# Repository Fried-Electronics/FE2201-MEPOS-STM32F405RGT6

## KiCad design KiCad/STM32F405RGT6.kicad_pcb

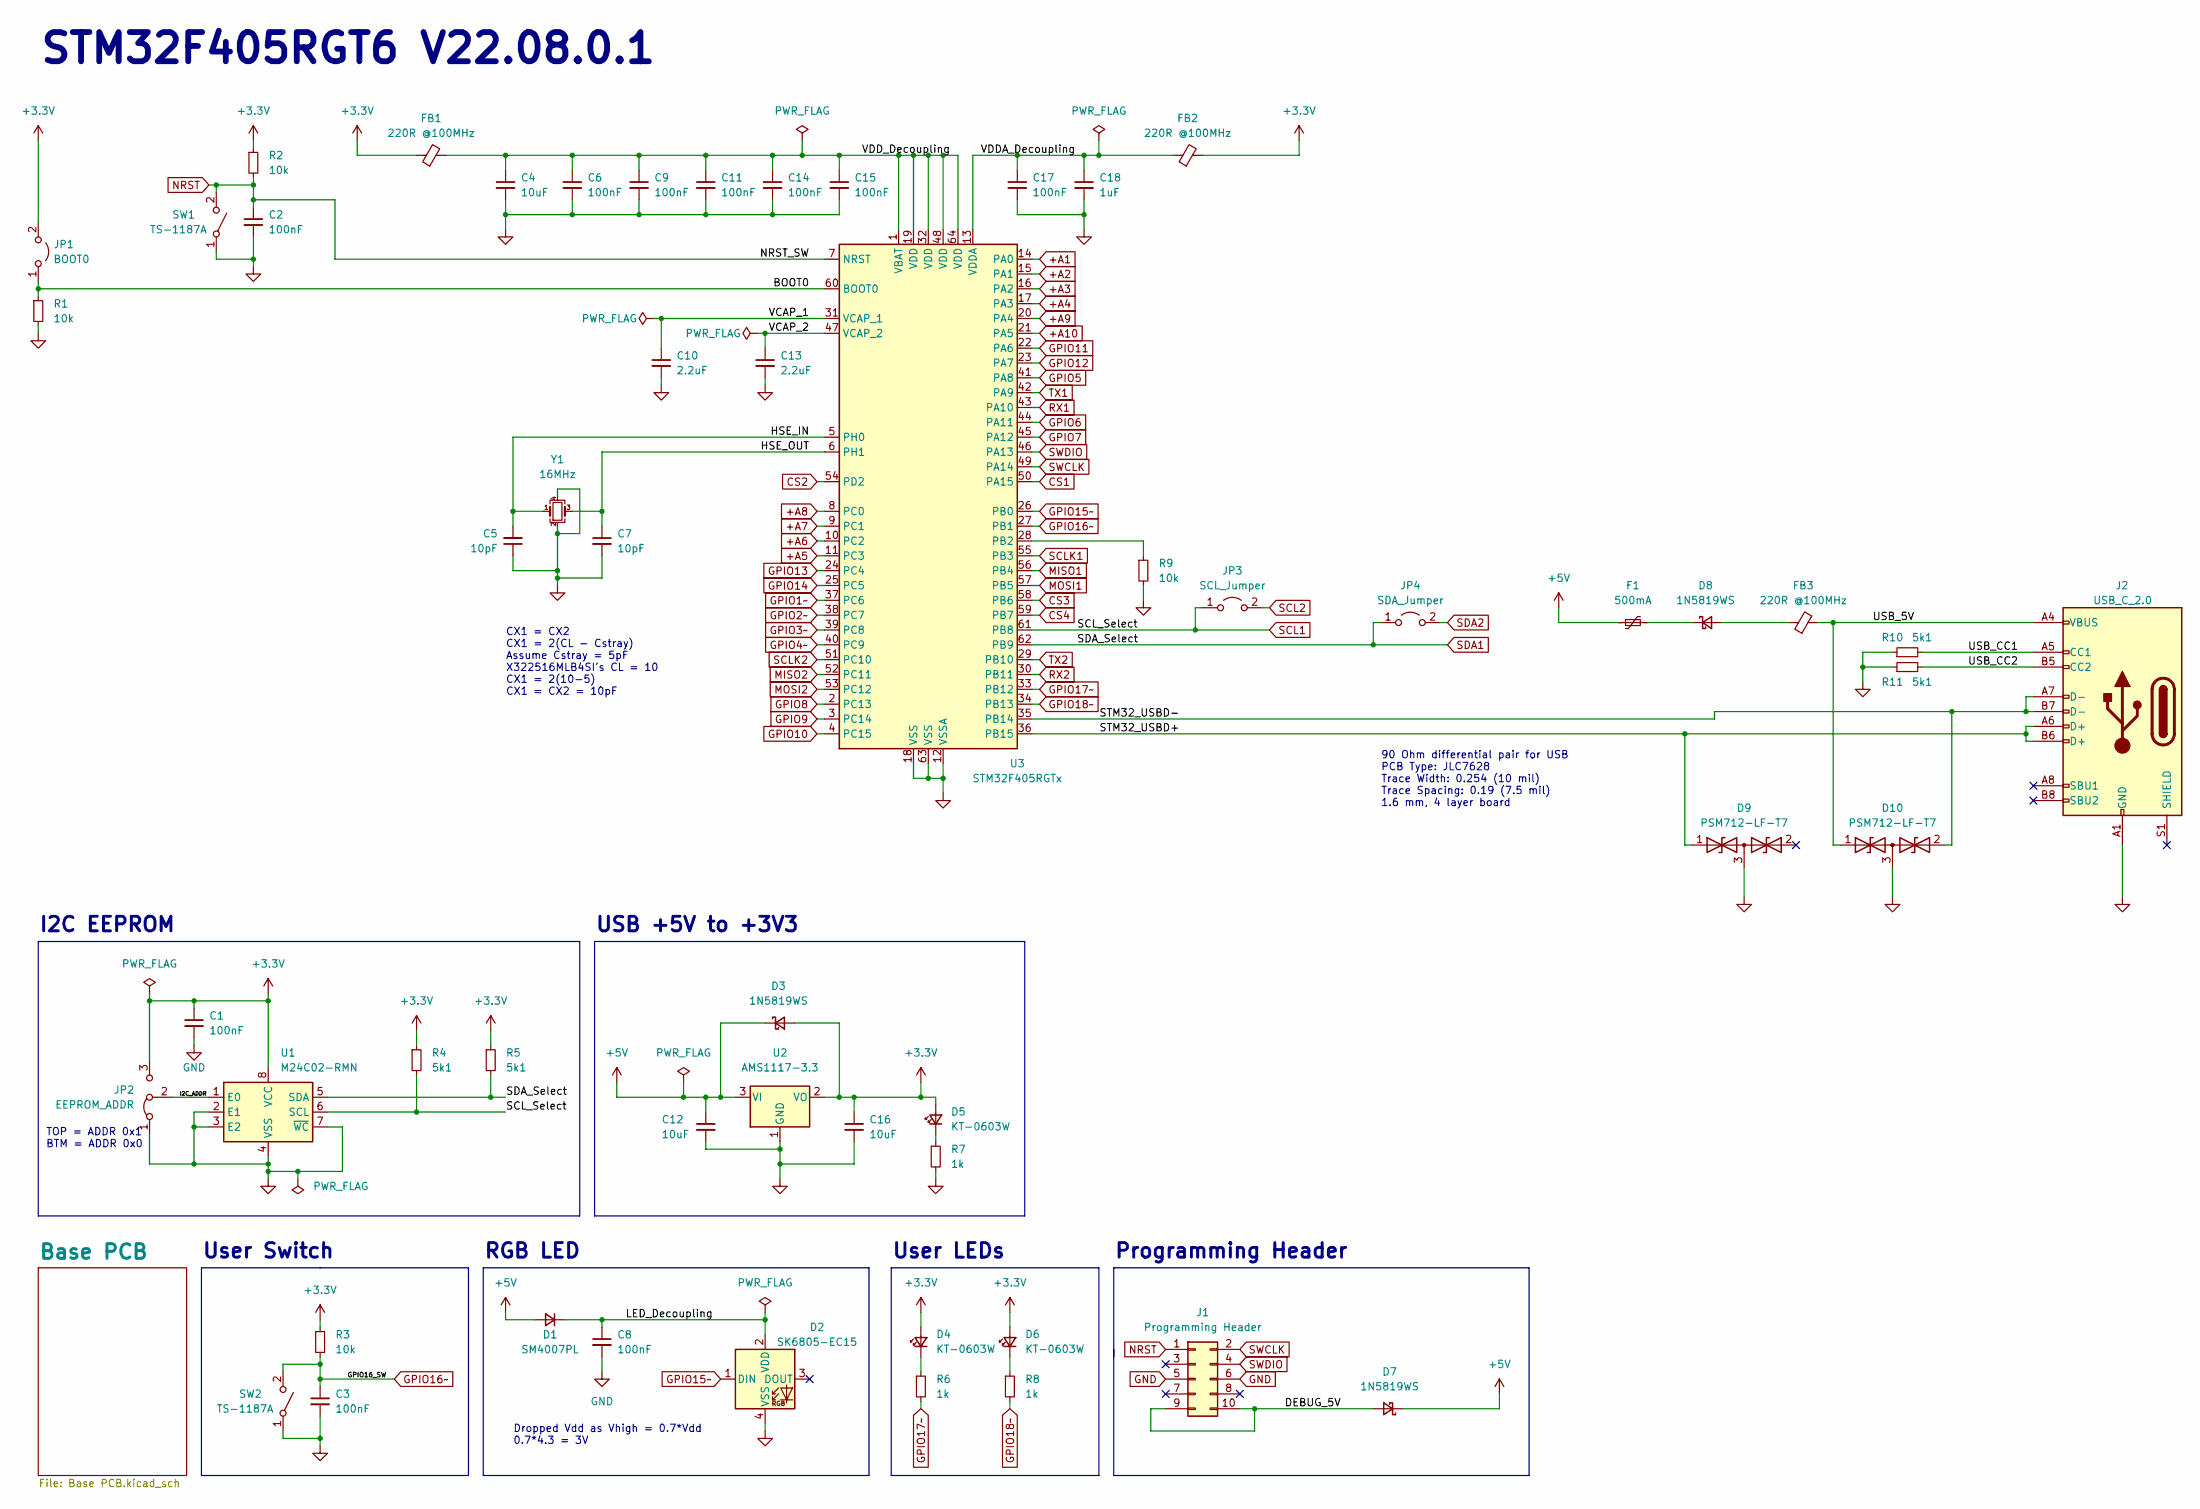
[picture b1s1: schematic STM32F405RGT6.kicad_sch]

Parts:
C1, C2, C3, C6, C8, C9, C11, C14, C15, C17: 100nF; C_0603_1608Metric; Part Number CC0603KRX7R9BB104; JLCPCB Part # C14663
C4, C12, C16: 10uF; C_0603_1608Metric; Part Number CL10A106KP8NNNC; JLCPCB Part # C19702
C5, C7: 10pF; C_0603_1608Metric; Part Number CL10C100JB8NNNC; JLCPCB Part # C1634
C10, C13: 2.2uF; C_0603_1608Metric; Part Number CL10A225KO8NNNC; JLCPCB Part # C23630
C18: 1uF; C_0603_1608Metric; Part Number CL10A105KB8NNNC; JLCPCB Part # C15849
D1: SM4007PL; D_SOD-123F; Part Number SM4007PL; JLCPCB Part # C64898
D2: SK6805-EC15
D3, D7, D8: 1N5819WS; D_SOD-323; Part Number 1N5819WS; JLCPCB Part # C191023
D4, D5, D6: KT-0603W; LED_0603_1608Metric; JLCPCB Part # C2290
D9, D10: PSM712-LF-T7; SOT-23; JLCPCB Part # C32677
F1: 500mA; Fuse_1206_3216Metric; Part Number JK-nSMD050-30; JLCPCB Part # C720075
FB1, FB2, FB3: 220R @100MHz; L_0603_1608Metric; Mouser Part Number 81-BLM18KG221SN1D
J1: Programming Header; PinHeader_2x05_P2.54mm_Horizontal; JLCPCB Part # C492433
J2: USB_C_2.0; USB_C_Receptacle_HRO_TYPE-C-31-M-12; Part Number TYPE-C-31-M-12; JLCPCB Part # C165948
JP1: BOOT0; PinHeader_1x02_P2.54mm_Vertical; Part Number PZ254V-11-02P; JLCPCB Part # C492401
JP2: EEPROM_ADDR; SolderJumper-3_P1.3mm_Bridged12_RoundedPad1.0x1.5mm
JP3: SCL_Jumper; SolderJumper-2_P1.3mm_Open_RoundedPad1.0x1.5mm
JP4: SDA_Jumper; SolderJumper-2_P1.3mm_Open_RoundedPad1.0x1.5mm
R1, R2, R3, R9: 10k; R_0603_1608Metric; Part Number 0603WAF1002T5E; JLCPCB Part # C25804
R4, R5, R10, R11: 5k1; R_0603_1608Metric; Part Number 0603WAF5101T5E; JLCPCB Part # C23186
R6, R7, R8: 1k; R_0603_1608Metric; Part Number 0603WAF1001T5E; JLCPCB Part # C21190
SW1, SW2: TS-1187A; SW_SPST_SKQG_WithStem; Part Number TS-1187A-B-A-B; JLCPCB Part # C318884
U1: M24C02-RMN; SOIC-8_3.9x4.9mm_P1.27mm; Mouser Part Number 511-M24C64-RMN6TP; JLCPCB Part # C79988
U2: AMS1117-3.3; SOT-223-3_TabPin2; Part Number AMS1117-3.3; JLCPCB Part # C6186
U3: STM32F405RGTx; LQFP-64_10x10mm_P0.5mm; Part Number STM32F405RGT6; JLCPCB Part # C15742
Y1: 16MHz; Crystal_SMD_3225-4Pin_3.2x2.5mm; Part Number X322516MLB4SI; JLCPCB Part # C13738

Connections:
+5V: C12.1, D1.2 (A), D3.1 (K), D7.1 (K), F1.1, U2.3 (VI); also elsewhere on the board
+A1: U3.14 (PA0); also elsewhere on the board
+A2: U3.15 (PA1); also elsewhere on the board
+A3: U3.16 (PA2); also elsewhere on the board
+A4: U3.17 (PA3); also elsewhere on the board
+A5: U3.11 (PC3); also elsewhere on the board
+A6: U3.10 (PC2); also elsewhere on the board
+A7: U3.9 (PC1); also elsewhere on the board
+A8: U3.8 (PC0); also elsewhere on the board
+A9: U3.20 (PA4); also elsewhere on the board
+A10: U3.21 (PA5); also elsewhere on the board
/BOOT0: JP1.1 (A), R1.1, U3.60 (BOOT0)
/DEBUG_5V: D7.2 (A), J1.9, J1.10
/HSE_IN: C5.2, U3.5 (PH0), Y1.1
/HSE_OUT: C7.1, U3.6 (PH1), Y1.3
/I2C_ADDR: JP2.2 (C), U1.1 (E0)
/LED_Decoupling: C8.1, D1.1 (K), D2.2 (VDD)
/STM32_USBD+: D9.1 (A1), J2.A6 (D+), J2.B6 (D+), U3.36 (PB15)
/STM32_USBD-: D10.2 (A2), J2.A7 (D-), J2.B7 (D-), U3.35 (PB14)
/USB_5V: D10.1 (A1), FB3.2, J2.A4 (VBUS), J2.A9 (VBUS), J2.B4 (VBUS), J2.B9 (VBUS)
/USB_CC1: J2.A5 (CC1), R10.2
/USB_CC2: J2.B5 (CC2), R11.2
/VCAP_1: C10.1, U3.31 (VCAP_1)
/VCAP_2: C13.1, U3.47 (VCAP_2)
/VDDA_Decoupling: C17.1, C18.1, FB2.1, U3.13 (VDDA)
/VDD_Decoupling: C4.1, C6.1, C9.1, C11.1, C14.1, C15.1, FB1.2, U3.1 (VBAT), U3.19 (VDD), U3.32 (VDD), U3.48 (VDD), U3.64 (VDD)
CS1: U3.50 (PA15); also elsewhere on the board
CS2: U3.54 (PD2); also elsewhere on the board
CS3: U3.58 (PB6); also elsewhere on the board
CS4: U3.59 (PB7); also elsewhere on the board
GND: C1.2, C2.2, C3.2, C4.2, C5.1, C6.2, C7.2, C8.2, C9.2, C10.2, C11.2, C12.2, C13.2, C14.2, C15.2, C16.2, C17.2, C18.2, D2.4 (VSS), D9.3 (common), D10.3 (common), J1.5, J1.6, J2.A1 (GND), J2.A12 (GND), J2.B1 (GND), J2.B12 (GND), JP2.1 (A), R1.2, R7.2, R9.2, R10.1, R11.1, SW1.1 (A), SW2.1 (A), U1.2 (E1), U1.3 (E2), U1.4 (VSS), U1.7 (~WC), U2.1 (GND), U3.12 (VSSA), U3.18 (VSS), U3.63 (VSS), Y1.2, Y1.4; also elsewhere on the board
GPIO1~: U3.37 (PC6); also elsewhere on the board
GPIO2~: U3.38 (PC7); also elsewhere on the board
GPIO3~: U3.39 (PC8); also elsewhere on the board
GPIO4~: U3.40 (PC9); also elsewhere on the board
GPIO5: U3.41 (PA8); also elsewhere on the board
GPIO6: U3.44 (PA11); also elsewhere on the board
GPIO7: U3.45 (PA12); also elsewhere on the board
GPIO8: U3.2 (PC13); also elsewhere on the board
GPIO9: U3.3 (PC14); also elsewhere on the board
GPIO10: U3.4 (PC15); also elsewhere on the board
GPIO11: U3.22 (PA6); also elsewhere on the board
GPIO12: U3.23 (PA7); also elsewhere on the board
GPIO13: U3.24 (PC4); also elsewhere on the board
GPIO14: U3.25 (PC5); also elsewhere on the board
GPIO15~: D2.1 (DIN), U3.26 (PB0); also elsewhere on the board
GPIO16~: C3.1, R3.2, SW2.2 (B), U3.27 (PB1); also elsewhere on the board
GPIO17~: R6.2, U3.33 (PB12); also elsewhere on the board
GPIO18~: R8.2, U3.34 (PB13); also elsewhere on the board
MISO1: U3.56 (PB4); also elsewhere on the board
MISO2: U3.52 (PC11); also elsewhere on the board
MOSI1: U3.57 (PB5); also elsewhere on the board
MOSI2: U3.53 (PC12); also elsewhere on the board
NRST: C2.1, J1.1, R2.2, SW1.2 (B), U3.7 (NRST)
unnamed: D4.1 (K), R6.1
unnamed: D5.1 (K), R7.1
unnamed: D6.1 (K), R8.1
unnamed: D8.1 (K), F1.2
unnamed: D8.2 (A), FB3.1
unnamed: R9.1, U3.28 (PB2)
RX1: U3.43 (PA10); also elsewhere on the board
RX2: U3.30 (PB11); also elsewhere on the board
SCL1: JP3.1 (A), R4.2, U1.6 (SCL), U3.61 (PB8); also elsewhere on the board
SCL2: JP3.2 (B); also elsewhere on the board
SCLK1: U3.55 (PB3); also elsewhere on the board
SCLK2: U3.51 (PC10); also elsewhere on the board
SDA1: JP4.1 (A), R5.2, U1.5 (SDA), U3.62 (PB9); also elsewhere on the board
SDA2: JP4.2 (B); also elsewhere on the board
SWCLK: J1.2, U3.49 (PA14)
SWDIO: J1.4, U3.46 (PA13)
TX1: U3.42 (PA9); also elsewhere on the board
TX2: U3.29 (PB10); also elsewhere on the board

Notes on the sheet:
USB +5V to +3V3
CX1 = CX2 CX1 = 2(CL - Cstray) Assume Cstray = 5pF X322516MLB4SI's CL = 10 CX1 = 2(10-5) CX1 = CX2 = 10pF
User LEDs
RGB LED
TOP = ADDR 0x1 BTM = ADDR 0x0
STM32F405RGT6 V22.08.0.1
I2C EEPROM
Programming Header
Dropped Vdd as Vhigh = 0.7*Vdd 0.7*4.3 = 3V
User Switch
90 Ohm differential pair for USB PCB Type: JLC7628 Trace Width: 0.254 (10 mil) Trace Spacing: 0.19 (7.5 mil) 1.6 mm, 4 layer board

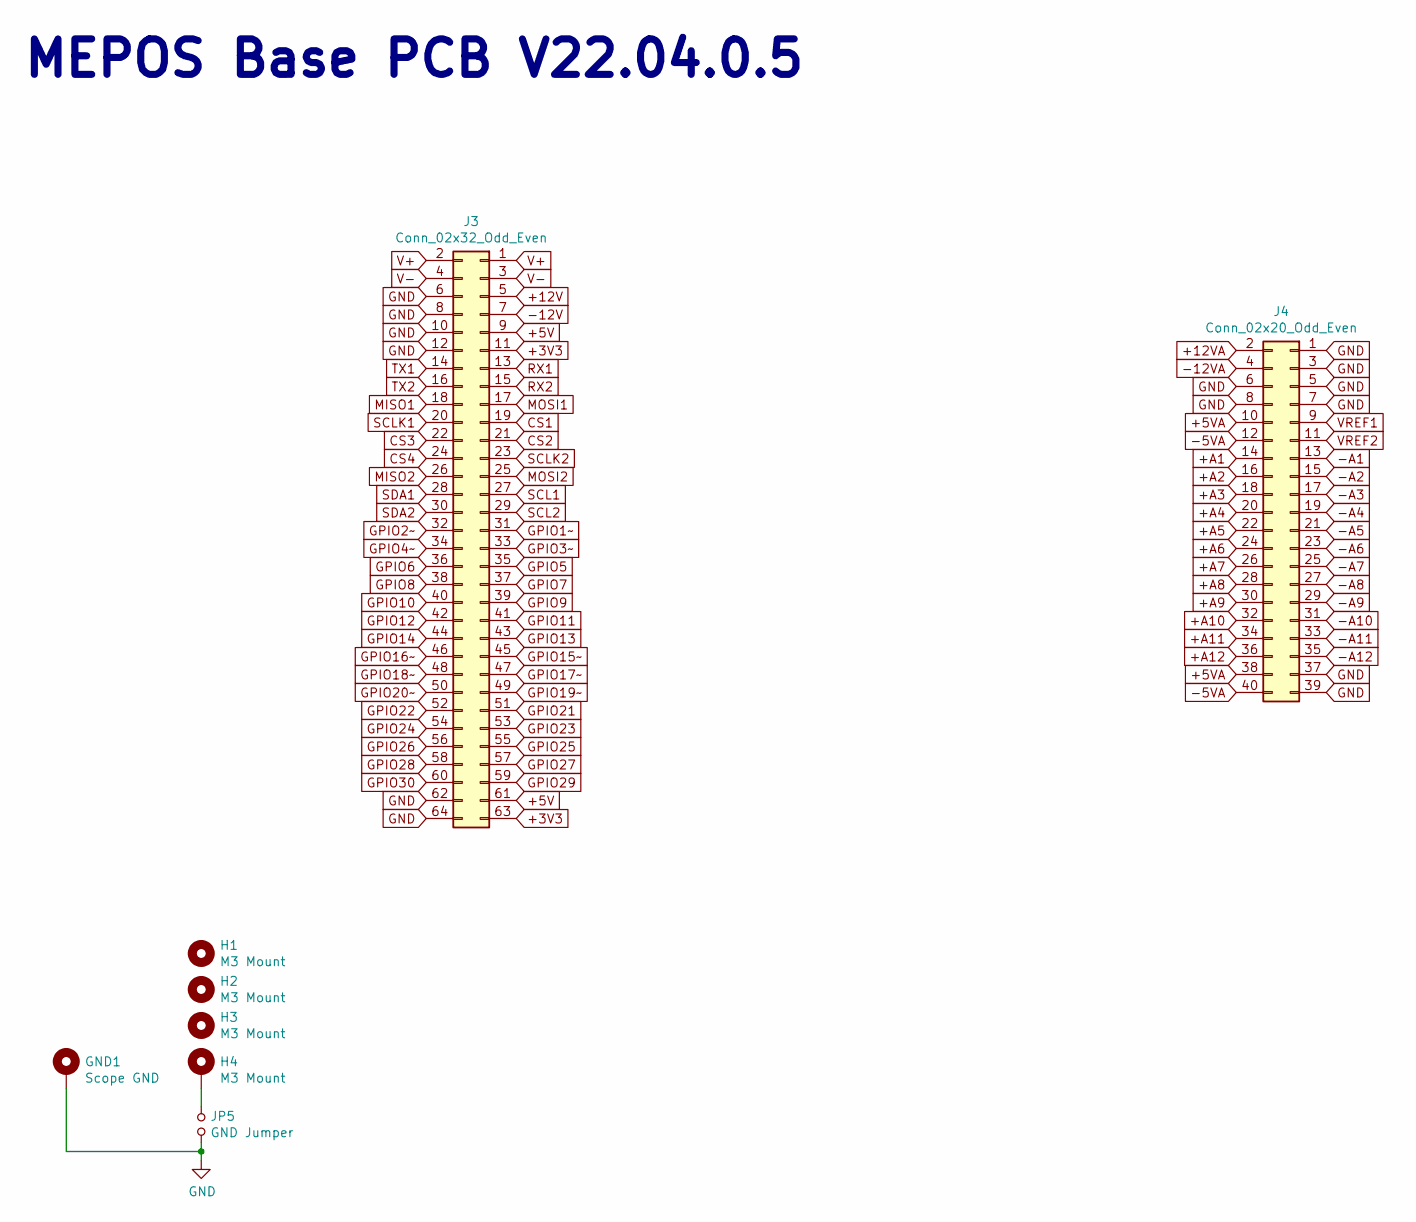
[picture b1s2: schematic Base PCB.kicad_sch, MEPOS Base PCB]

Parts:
GND1: Scope GND; Scope_GND
H1, H2, H3, H4: M3 Mount; MountingHole_3.2mm_M3_Pad
J3: Conn_02x32_Odd_Even; PinSocket_2x32_P2.54mm_Vertical
J4: Conn_02x20_Odd_Even; PinSocket_2x20_P2.54mm_Vertical
JP5: GND Jumper; TestPoint_2Pads_Pitch2.54mm_Drill0.8mm

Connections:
+5V: J3.9, J3.61; also elsewhere on the board
+5VA: J4.10, J4.38
+12V: J3.5
+12VA: J4.2
+A1: J4.14; also elsewhere on the board
+A2: J4.16; also elsewhere on the board
+A3: J4.18; also elsewhere on the board
+A4: J4.20; also elsewhere on the board
+A5: J4.22; also elsewhere on the board
+A6: J4.24; also elsewhere on the board
+A7: J4.26; also elsewhere on the board
+A8: J4.28; also elsewhere on the board
+A9: J4.30; also elsewhere on the board
+A10: J4.32; also elsewhere on the board
+A11: J4.34
+A12: J4.36
-5VA: J4.12, J4.40
-12V: J3.7
-12VA: J4.4
-A1: J4.13
-A2: J4.15
-A3: J4.17
-A4: J4.19
-A5: J4.21
-A6: J4.23
-A7: J4.25
-A8: J4.27
-A9: J4.29
-A10: J4.31
-A11: J4.33
-A12: J4.35
CS1: J3.19; also elsewhere on the board
CS2: J3.21; also elsewhere on the board
CS3: J3.22; also elsewhere on the board
CS4: J3.24; also elsewhere on the board
GND: GND1.1, J3.6, J3.8, J3.10, J3.12, J3.62, J3.64, J4.1, J4.3, J4.5, J4.6, J4.7, J4.8, J4.37, J4.39, JP5.2; also elsewhere on the board
GPIO1~: J3.31; also elsewhere on the board
GPIO2~: J3.32; also elsewhere on the board
GPIO3~: J3.33; also elsewhere on the board
GPIO4~: J3.34; also elsewhere on the board
GPIO5: J3.35; also elsewhere on the board
GPIO6: J3.36; also elsewhere on the board
GPIO7: J3.37; also elsewhere on the board
GPIO8: J3.38; also elsewhere on the board
GPIO9: J3.39; also elsewhere on the board
GPIO10: J3.40; also elsewhere on the board
GPIO11: J3.41; also elsewhere on the board
GPIO12: J3.42; also elsewhere on the board
GPIO13: J3.43; also elsewhere on the board
GPIO14: J3.44; also elsewhere on the board
GPIO15~: J3.45; also elsewhere on the board
GPIO16~: J3.46; also elsewhere on the board
GPIO17~: J3.47; also elsewhere on the board
GPIO18~: J3.48; also elsewhere on the board
GPIO19~: J3.49
GPIO20~: J3.50
GPIO21: J3.51
GPIO22: J3.52
GPIO23: J3.53
GPIO24: J3.54
GPIO25: J3.55
GPIO26: J3.56
GPIO27: J3.57
GPIO28: J3.58
GPIO29: J3.59
GPIO30: J3.60
MISO1: J3.18; also elsewhere on the board
MISO2: J3.26; also elsewhere on the board
MOSI1: J3.17; also elsewhere on the board
MOSI2: J3.25; also elsewhere on the board
unnamed: H4.1, JP5.1
RX1: J3.13; also elsewhere on the board
RX2: J3.15; also elsewhere on the board
SCL1: J3.27; also elsewhere on the board
SCL2: J3.29; also elsewhere on the board
SCLK1: J3.20; also elsewhere on the board
SCLK2: J3.23; also elsewhere on the board
SDA1: J3.28; also elsewhere on the board
SDA2: J3.30; also elsewhere on the board
TX1: J3.14; also elsewhere on the board
TX2: J3.16; also elsewhere on the board
V+: J3.1, J3.2
V-: J3.3, J3.4
VREF1: J4.9
VREF2: J4.11

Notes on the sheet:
MEPOS Base PCB V22.04.0.5

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
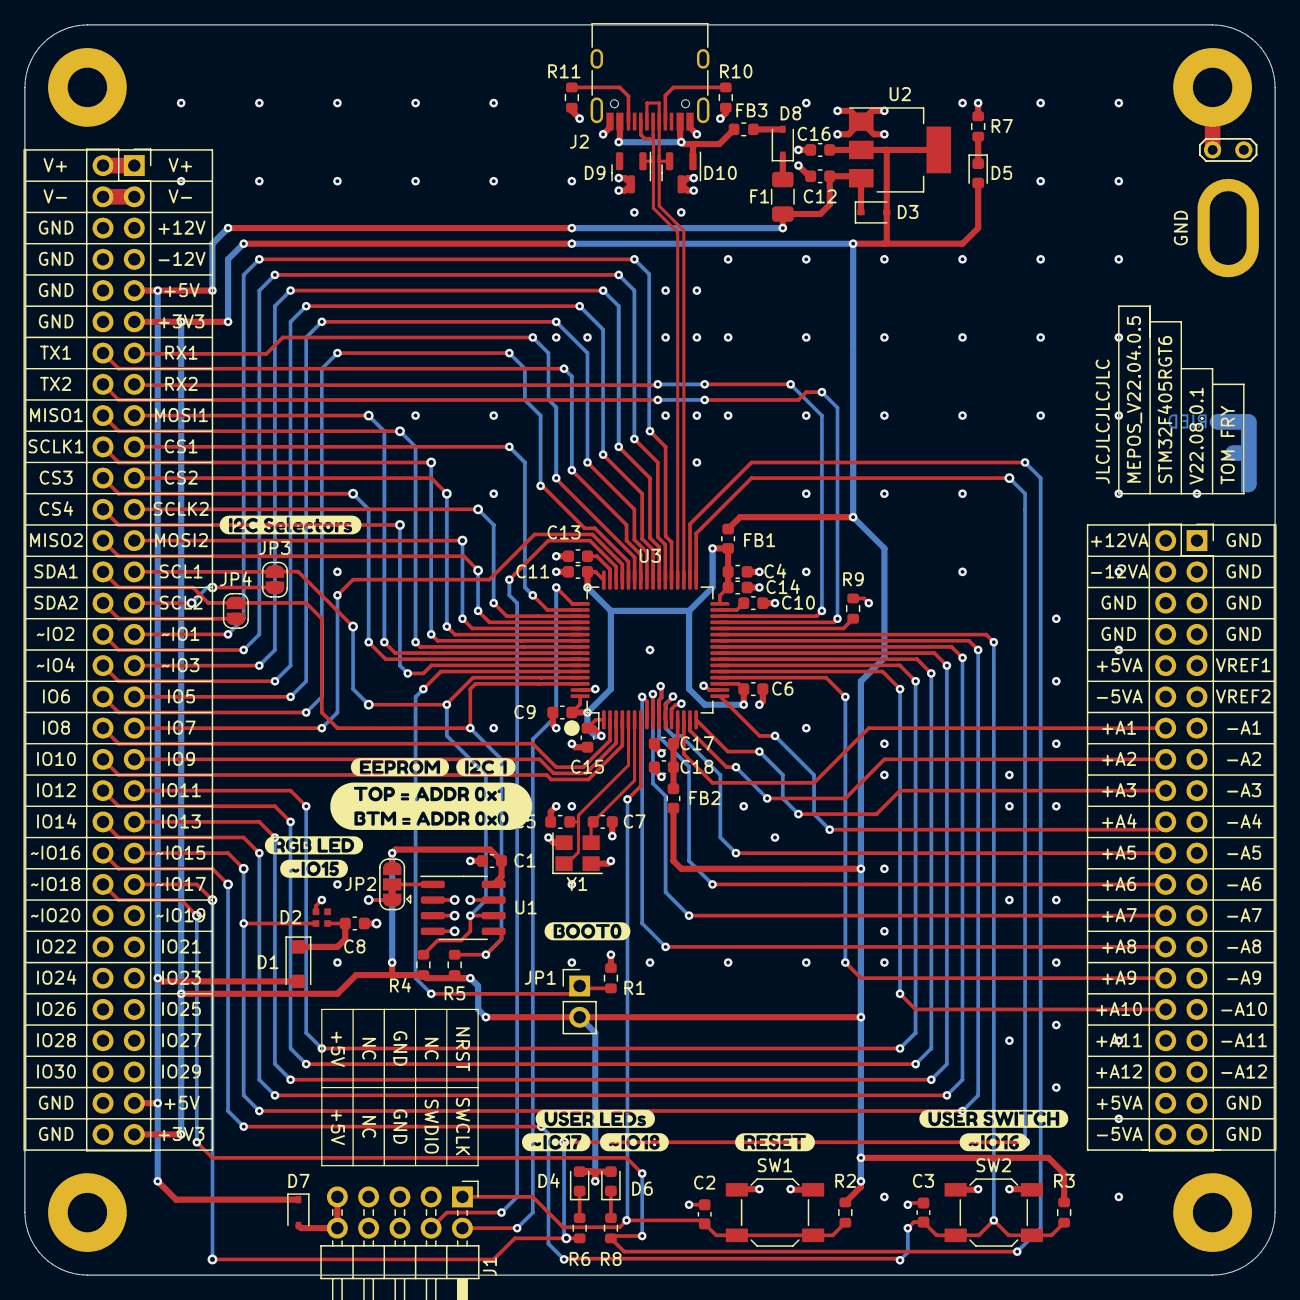
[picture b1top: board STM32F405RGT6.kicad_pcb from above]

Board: 4 copper layers, 101.6 x 101.6 mm, 77 parts (1 on the bottom side), 78 nets.

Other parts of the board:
KiCad_Logo: KiCad-Logo2_5mm_SilkScreen
kibuzzard-630B16ED: G***; kibuzzard-630B16ED
kibuzzard-630B17C2: G***; kibuzzard-630B17C2
kibuzzard-630B17D9: G***; kibuzzard-630B17D9
kibuzzard-630B17E2: G***; kibuzzard-630B17E2
kibuzzard-630B175D: G***; kibuzzard-630B175D
kibuzzard-630B176C: G***; kibuzzard-630B176C
kibuzzard-630B178A: G***; kibuzzard-630B178A
kibuzzard-630B1710: G***; kibuzzard-630B1710
kibuzzard-630B1728: G***; kibuzzard-630B1728
kibuzzard-630B1736: G***; kibuzzard-630B1736
kibuzzard-630B1749: G***; kibuzzard-630B1749
kibuzzard-630B1806: G***; kibuzzard-630B1806
kibuzzard-632AC88F: G***; kibuzzard-632AC88F

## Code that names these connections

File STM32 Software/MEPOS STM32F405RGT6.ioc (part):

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Mcu.Name=STM32F405RGTx
Mcu.Package=LQFP64
Mcu.UserName=STM32F405RGTx
PA0-WKUP.GPIOParameters=GPIO_Label
PA0-WKUP.GPIO_Label=A1
PA0-WKUP.Signal=ADCx_IN0
PA1.GPIOParameters=GPIO_Label
PA1.GPIO_Label=A2
PA1.Signal=ADCx_IN1
PA10.GPIOParameters=GPIO_Label
PA10.GPIO_Label=RX1
PA10.Mode=Asynchronous
PA10.Signal=USART1_RX
PA11.GPIOParameters=GPIO_Label
PA11.GPIO_Label=GPIO6
PA11.Signal=GPIO_Output
PA12.GPIOParameters=GPIO_Label
PA12.GPIO_Label=GPIO7
PA12.Signal=GPIO_Output
PA13.GPIOParameters=GPIO_Label
PA13.GPIO_Label=SWDIO
PA13.Mode=Trace_Asynchronous_SW
PA13.Signal=SYS_JTMS-SWDIO
PA14.GPIOParameters=GPIO_Label
PA14.GPIO_Label=SWCLK
PA14.Mode=Trace_Asynchronous_SW
PA14.Signal=SYS_JTCK-SWCLK
PA15.GPIOParameters=GPIO_Label
PA15.GPIO_Label=GPIO8
PA15.Signal=S_TIM2_CH1_ETR
PA2.GPIOParameters=GPIO_Label
PA2.GPIO_Label=A3
PA2.Signal=ADCx_IN2
PA3.GPIOParameters=GPIO_Label
PA3.GPIO_Label=A4
PA3.Signal=ADCx_IN3
PA4.GPIOParameters=GPIO_Label
PA4.GPIO_Label=A9
PA4.Signal=COMP_DAC1_group
PA5.GPIOParameters=GPIO_Label
PA5.GPIO_Label=A10
PA5.Signal=COMP_DAC2_group
PA6.GPIOParameters=GPIO_Label
PA6.GPIO_Label=GPIO15
PA6.Signal=GPIO_Output
PA7.GPIOParameters=GPIO_Label
PA7.GPIO_Label=GPIO16
PA7.Signal=GPIO_Output
PA8.GPIOParameters=GPIO_Label
PA8.GPIO_Label=GPIO5
PA8.Signal=S_TIM1_CH1
PA9.GPIOParameters=GPIO_Label
PA9.GPIO_Label=TX1
PA9.Mode=Asynchronous
PA9.Signal=USART1_TX
PB0.GPIOParameters=GPIO_Label
PB0.GPIO_Label=GPIO19~
PB0.Signal=GPIO_Output
PB1.GPIOParameters=GPIO_Label
PB1.GPIO_Label=GPIO20~
PB1.Signal=GPIO_Output
PB10.GPIOParameters=GPIO_Label
PB10.GPIO_Label=TX2
PB10.Mode=Asynchronous
PB10.Signal=USART3_TX
PB11.GPIOParameters=GPIO_Label
PB11.GPIO_Label=RX2
PB11.Mode=Asynchronous
PB11.Signal=USART3_RX
PB12.GPIOParameters=GPIO_Label
PB12.GPIO_Label=GPIO21
PB12.Mode=CAN_Activate
PB12.Signal=CAN2_RX
PB13.GPIOParameters=GPIO_Label
PB13.GPIO_Label=GPIO22
PB13.Mode=CAN_Activate
PB13.Signal=CAN2_TX
PB14.Mode=Device_Only_FS
PB14.Signal=USB_OTG_HS_DM
PB15.Mode=Device_Only_FS
PB15.Signal=USB_OTG_HS_DP
PB2.GPIOParameters=GPIO_Label
PB2.GPIO_Label=BOOT1
PB2.Signal=GPIO_Input
PB3.GPIOParameters=GPIO_Label
PB3.GPIO_Label=SWO
PB3.Mode=Trace_Asynchronous_SW
PB3.Signal=SYS_JTDO-SWO
PB4.GPIOParameters=GPIO_Label
PB4.GPIO_Label=CS2
PB4.Signal=GPIO_Output
PB5.GPIOParameters=GPIO_Label
PB5.GPIO_Label=GPIO9
PB5.Signal=GPIO_Output
PB6.GPIOParameters=GPIO_Label
PB6.GPIO_Label=GPIO10
PB6.Signal=GPIO_Output
PB7.GPIOParameters=GPIO_Label
PB7.GPIO_Label=GPIO11
PB7.Signal=GPIO_Output
PB8.GPIOParameters=GPIO_Label
PB8.GPIO_Label=SCL1
PB8.Mode=I2C
PB8.Signal=I2C1_SCL
PB9.GPIOParameters=GPIO_Label
PB9.GPIO_Label=SDA1
PB9.Mode=I2C
PB9.Signal=I2C1_SDA
PC0.GPIOParameters=GPIO_Label
PC0.GPIO_Label=A8
PC0.Signal=ADCx_IN10
PC1.GPIOParameters=GPIO_Label
PC1.GPIO_Label=A7
PC1.Signal=ADCx_IN11
PC10.GPIOParameters=GPIO_Label
PC10.GPIO_Label=SCLK1
PC10.Mode=Full_Duplex_Master
PC10.Signal=SPI3_SCK
PC11.GPIOParameters=GPIO_Label
PC11.GPIO_Label=MISO1
PC11.Mode=Full_Duplex_Master
PC11.Signal=SPI3_MISO
PC12.GPIOParameters=GPIO_Label
PC12.GPIO_Label=MOSI1
PC12.Mode=Full_Duplex_Master
PC12.Signal=SPI3_MOSI
PC13-ANTI_TAMP.GPIOParameters=GPIO_Label
PC13-ANTI_TAMP.GPIO_Label=GPIO12
PC13-ANTI_TAMP.Signal=GPIO_Output
PC14-OSC32_IN.GPIOParameters=GPIO_Label
PC14-OSC32_IN.GPIO_Label=GPIO13
PC14-OSC32_IN.Signal=GPIO_Output
PC15-OSC32_OUT.GPIOParameters=GPIO_Label
PC15-OSC32_OUT.GPIO_Label=GPIO14
PC15-OSC32_OUT.Signal=GPIO_Output
PC2.GPIOParameters=GPIO_Label
PC2.GPIO_Label=A6
PC2.Signal=ADCx_IN12
PC3.GPIOParameters=GPIO_Label
PC3.GPIO_Label=A5
PC3.Signal=ADCx_IN13
PC4.GPIOParameters=GPIO_Label
PC4.GPIO_Label=GPIO17~
PC4.Signal=GPIO_Output
PC5.GPIOParameters=GPIO_Label
PC5.GPIO_Label=GPIO18~
PC5.Signal=GPIO_Output
PC6.GPIOParameters=GPIO_Label
PC6.GPIO_Label=GPIO1~
PC6.Signal=S_TIM3_CH1
PC7.GPIOParameters=GPIO_Label
PC7.GPIO_Label=GPIO2~
PC7.Signal=S_TIM3_CH2
PC8.GPIOParameters=GPIO_Label
PC8.GPIO_Label=GPIO3~
PC8.Signal=S_TIM3_CH3
PC9.GPIOParameters=GPIO_Label
PC9.GPIO_Label=GPIO4~
PC9.Signal=S_TIM3_CH4
PD2.GPIOParameters=GPIO_Label
PD2.GPIO_Label=CS1
PD2.Signal=GPIO_Output
PH0-OSC_IN.Mode=HSE-External-Oscillator
PH0-OSC_IN.Signal=RCC_OSC_IN
PH1-OSC_OUT.Mode=HSE-External-Oscillator
PH1-OSC_OUT.Signal=RCC_OSC_OUT
RCC.HSE_VALUE=25000000
RCC.SYSCLKFreq_VALUE=168000000
RCC.SYSCLKSource=RCC_SYSCLKSOURCE_PLLCLK
board=custom

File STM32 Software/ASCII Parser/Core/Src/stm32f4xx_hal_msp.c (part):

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    __HAL_RCC_GPIOC_CLK_ENABLE();
    __HAL_RCC_GPIOA_CLK_ENABLE();
    /**ADC1 GPIO Configuration
    PC0     ------> ADC1_IN10
    PC1     ------> ADC1_IN11
    PC2     ------> ADC1_IN12
    PC3     ------> ADC1_IN13
    PA0-WKUP     ------> ADC1_IN0
    PA1     ------> ADC1_IN1
    PA2     ------> ADC1_IN2
    PA3     ------> ADC1_IN3
    */
    GPIO_InitStruct.Pin = A8_Pin|A7_Pin|A6_Pin|A5_Pin;
    GPIO_InitStruct.Mode = GPIO_MODE_ANALOG;
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    __HAL_RCC_ADC1_CLK_DISABLE();

    /**ADC1 GPIO Configuration
    PC0     ------> ADC1_IN10
    PC1     ------> ADC1_IN11
    PC2     ------> ADC1_IN12
    PC3     ------> ADC1_IN13
    PA0-WKUP     ------> ADC1_IN0
    PA1     ------> ADC1_IN1
    PA2     ------> ADC1_IN2
    PA3     ------> ADC1_IN3
    */
    HAL_GPIO_DeInit(GPIOC, A8_Pin|A7_Pin|A6_Pin|A5_Pin);

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
    __HAL_RCC_GPIOB_CLK_ENABLE();
    /**CAN2 GPIO Configuration
    PB12     ------> CAN2_RX
    PB13     ------> CAN2_TX
    */
    GPIO_InitStruct.Pin = GPIO17__Pin|GPIO18__Pin;
    GPIO_InitStruct.Mode = GPIO_MODE_AF_PP;
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    __HAL_RCC_CAN1_CLK_DISABLE();

    /**CAN2 GPIO Configuration
    PB12     ------> CAN2_RX
    PB13     ------> CAN2_TX
    */
    HAL_GPIO_DeInit(GPIOB, GPIO17__Pin|GPIO18__Pin);

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
    __HAL_RCC_GPIOA_CLK_ENABLE();
    /**DAC GPIO Configuration
    PA4     ------> DAC_OUT1
    PA5     ------> DAC_OUT2
    */
    GPIO_InitStruct.Pin = A9_Pin|A10_Pin;
    GPIO_InitStruct.Mode = GPIO_MODE_ANALOG;
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    __HAL_RCC_DAC_CLK_DISABLE();

    /**DAC GPIO Configuration
    PA4     ------> DAC_OUT1
    PA5     ------> DAC_OUT2
    */
    HAL_GPIO_DeInit(GPIOA, A9_Pin|A10_Pin);

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
    __HAL_RCC_GPIOB_CLK_ENABLE();
    /**I2C1 GPIO Configuration
    PB8     ------> I2C1_SCL
    PB9     ------> I2C1_SDA
    */
    GPIO_InitStruct.Pin = SCL1_2_Pin|SDA1_2_Pin;
    GPIO_InitStruct.Mode = GPIO_MODE_AF_OD;
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    __HAL_RCC_I2C1_CLK_DISABLE();

    /**I2C1 GPIO Configuration
    PB8     ------> I2C1_SCL
    PB9     ------> I2C1_SDA
    */
    HAL_GPIO_DeInit(SCL1_2_GPIO_Port, SCL1_2_Pin);

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
    __HAL_RCC_GPIOB_CLK_ENABLE();
    /**SPI1 GPIO Configuration
    PB3     ------> SPI1_SCK
    PB4     ------> SPI1_MISO
    PB5     ------> SPI1_MOSI
    */
    GPIO_InitStruct.Pin = SCLK1_Pin|MISO1_Pin|MOSI1_Pin;
    GPIO_InitStruct.Mode = GPIO_MODE_AF_PP;
    GPIO_InitStruct.Pull = GPIO_NOPULL;
    GPIO_InitStruct.Speed = GPIO_SPEED_FREQ_VERY_HIGH;
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
    __HAL_RCC_GPIOC_CLK_ENABLE();
    /**SPI3 GPIO Configuration
    PC10     ------> SPI3_SCK
    PC11     ------> SPI3_MISO
    PC12     ------> SPI3_MOSI
    */
    GPIO_InitStruct.Pin = SCLK2_Pin|MISO2_Pin|MOSI2_Pin;
    GPIO_InitStruct.Mode = GPIO_MODE_AF_PP;
    GPIO_InitStruct.Pull = GPIO_NOPULL;
    GPIO_InitStruct.Speed = GPIO_SPEED_FREQ_VERY_HIGH;
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    __HAL_RCC_SPI1_CLK_DISABLE();

    /**SPI1 GPIO Configuration
    PB3     ------> SPI1_SCK
    PB4     ------> SPI1_MISO
    PB5     ------> SPI1_MOSI
    */
    HAL_GPIO_DeInit(GPIOB, SCLK1_Pin|MISO1_Pin|MOSI1_Pin);

  /* USER CODE BEGIN SPI1_MspDeInit 1 */

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    __HAL_RCC_SPI3_CLK_DISABLE();

    /**SPI3 GPIO Configuration
    PC10     ------> SPI3_SCK
    PC11     ------> SPI3_MISO
    PC12     ------> SPI3_MOSI
    */
    HAL_GPIO_DeInit(GPIOC, SCLK2_Pin|MISO2_Pin|MOSI2_Pin);

  /* USER CODE BEGIN SPI3_MspDeInit 1 */

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  /* USER CODE END TIM1_MspPostInit 0 */
    __HAL_RCC_GPIOA_CLK_ENABLE();
    /**TIM1 GPIO Configuration
    PA8     ------> TIM1_CH1
    */
    GPIO_InitStruct.Pin = GPIO5_Pin;
    GPIO_InitStruct.Mode = GPIO_MODE_AF_PP;
    GPIO_InitStruct.Pull = GPIO_NOPULL;
    GPIO_InitStruct.Speed = GPIO_SPEED_FREQ_LOW;
    GPIO_InitStruct.Alternate = GPIO_AF1_TIM1;
    HAL_GPIO_Init(GPIO5_GPIO_Port, &GPIO_InitStruct);

  /* USER CODE BEGIN TIM1_MspPostInit 1 */

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
    __HAL_RCC_GPIOC_CLK_ENABLE();
    /**TIM3 GPIO Configuration
    PC6     ------> TIM3_CH1
    PC7     ------> TIM3_CH2
    PC8     ------> TIM3_CH3
    PC9     ------> TIM3_CH4
    */
    GPIO_InitStruct.Pin = GPIO1__Pin|GPIO2__Pin|GPIO3__Pin|GPIO4__Pin;
    GPIO_InitStruct.Mode = GPIO_MODE_AF_PP;
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
    __HAL_RCC_GPIOA_CLK_ENABLE();
    /**USART1 GPIO Configuration
    PA9     ------> USART1_TX
    PA10     ------> USART1_RX
    */
    GPIO_InitStruct.Pin = TX1_Pin|RX1_Pin;
    GPIO_InitStruct.Mode = GPIO_MODE_AF_PP;
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
    __HAL_RCC_GPIOB_CLK_ENABLE();
    /**USART3 GPIO Configuration
    PB10     ------> USART3_TX
    PB11     ------> USART3_RX
    */
    GPIO_InitStruct.Pin = TX2_Pin|RX2_Pin;
    GPIO_InitStruct.Mode = GPIO_MODE_AF_PP;
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    __HAL_RCC_USART1_CLK_DISABLE();

    /**USART1 GPIO Configuration
    PA9     ------> USART1_TX
    PA10     ------> USART1_RX
    */
    HAL_GPIO_DeInit(GPIOA, TX1_Pin|RX1_Pin);

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    __HAL_RCC_USART3_CLK_DISABLE();

    /**USART3 GPIO Configuration
    PB10     ------> USART3_TX
    PB11     ------> USART3_RX
    */
    HAL_GPIO_DeInit(GPIOB, TX2_Pin|RX2_Pin);

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
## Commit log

2022-05-23 Create Project Files
2022-05-23 Added prototype components to schematic
2022-05-23 started adding functions to pins
2022-05-23 Added Components to the Schematic and PCB
2022-05-24 Updated Schematic and PCB
2022-06-09 Added components to schematic
2022-06-09 Updated STM32 Cube and KiCad files
2022-06-10 Update Schematic and PCB
2022-06-28 Updated PCB and Schematic
2022-06-30 Removed FTDI chip and rearranged pinout
2022-06-30 Updated Schematic to STM32 software
2022-07-01 Updated Schematic and BOM
2022-07-11 Added CCU Resistors
2022-07-11 Updated to newer MEPOS Library
2022-07-11 added USB 3D model and PTC fuse
2022-07-12 added USB differential pair info
2022-07-12 Added stack up and differential pair size
2022-07-12 Added part numbers to most parts
2022-07-12 Updated ADC pinning for better routing
2022-07-12 Added VCP Driver
2022-07-14 Started Routing
2022-07-14 Updated Routing
2022-07-21 Updated PCB
2022-07-26 Fixed some DRC errors
2022-08-26 Changed Pin Mapping
2022-08-27 Changed some components
    added a PNP mosfet onto the onboard 3.3V regulator to stop the diode drop.
    changed the ESD protection on the USB to allow for more clearance
2022-08-28 Added Datasheets
2022-08-28 Updated silkscreen text to labels
2022-08-30 Schematic and BOM Checked
2022-08-30 Update STM32F405RGT6.kicad_pcb
    Stitched GND planes together
2022-08-30 Updated title block and created PDF
2022-08-30 Generated Gerbers
2022-08-30 Update STM32F405RGT6.kicad_sch
    Updated title block
2022-08-30 Changed SK6805 Footprint and plotted
2022-08-30 Implement LineCodingBuffer
    Sets the line coding for communication over USB
2022-08-30 Update main.c
    Added Extern Tx and Rx buffers and head and tail variables
2022-08-30 Update main.c
    Added comments for CDC Variables
2022-08-30 Update usbd_cdc_if.c
    Added external variables from Main.c and added
2022-08-30 Fixed spelling
    Added decrement header to .h file
2022-08-30 Update usbd_cdc_if.c
    Added some functionality to inc and dec head
2022-08-30 Changed Structure
    Moved STM32 files into "DEFAULT" Folder so that other projects like "ASCII Parser" can be built from it
2022-08-30 Updated Variable locations
2022-08-30 Added check available function
2022-08-30 Started command buffer code
2022-08-30 Added Pictures
2022-09-09 Updated Debug Header
2022-09-09 Fixed debug silkscreen
2022-09-13 Created RGB LED project
2022-09-13 Update main.c
    removed lines that shouldnt be there
2022-09-13 Created Header and source files
2022-09-13 Update RGB_LED.h
    Create RGB_LED struct
2022-09-14 Code now works on board
2022-09-14 Implemented Rainbow function
2022-09-14 Rough working rainbow LED
2022-09-21 Changed J1 to right angle connector and created 3D model
2022-09-21 Updated 3D model
2022-09-21 Updated offset
2022-10-31 Create EEPROM Project
2022-10-31 Configure Code
2022-10-31 Implement Byte Read and Write
2022-11-01 works with HAL Delay?
2022-11-02 created much better byte read and write code
2022-11-02 Create Page Write Code
2022-11-02 Create write All
2022-11-04 Updated EEPROM Code

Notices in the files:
STM32 Software/ASCII Parser/Core/Src/stm32f4xx_hal_msp.c:
Copyright (c) 2022 STMicroelectronics.
All rights reserved.
This software is licensed under terms that can be found in the LICENSE file
